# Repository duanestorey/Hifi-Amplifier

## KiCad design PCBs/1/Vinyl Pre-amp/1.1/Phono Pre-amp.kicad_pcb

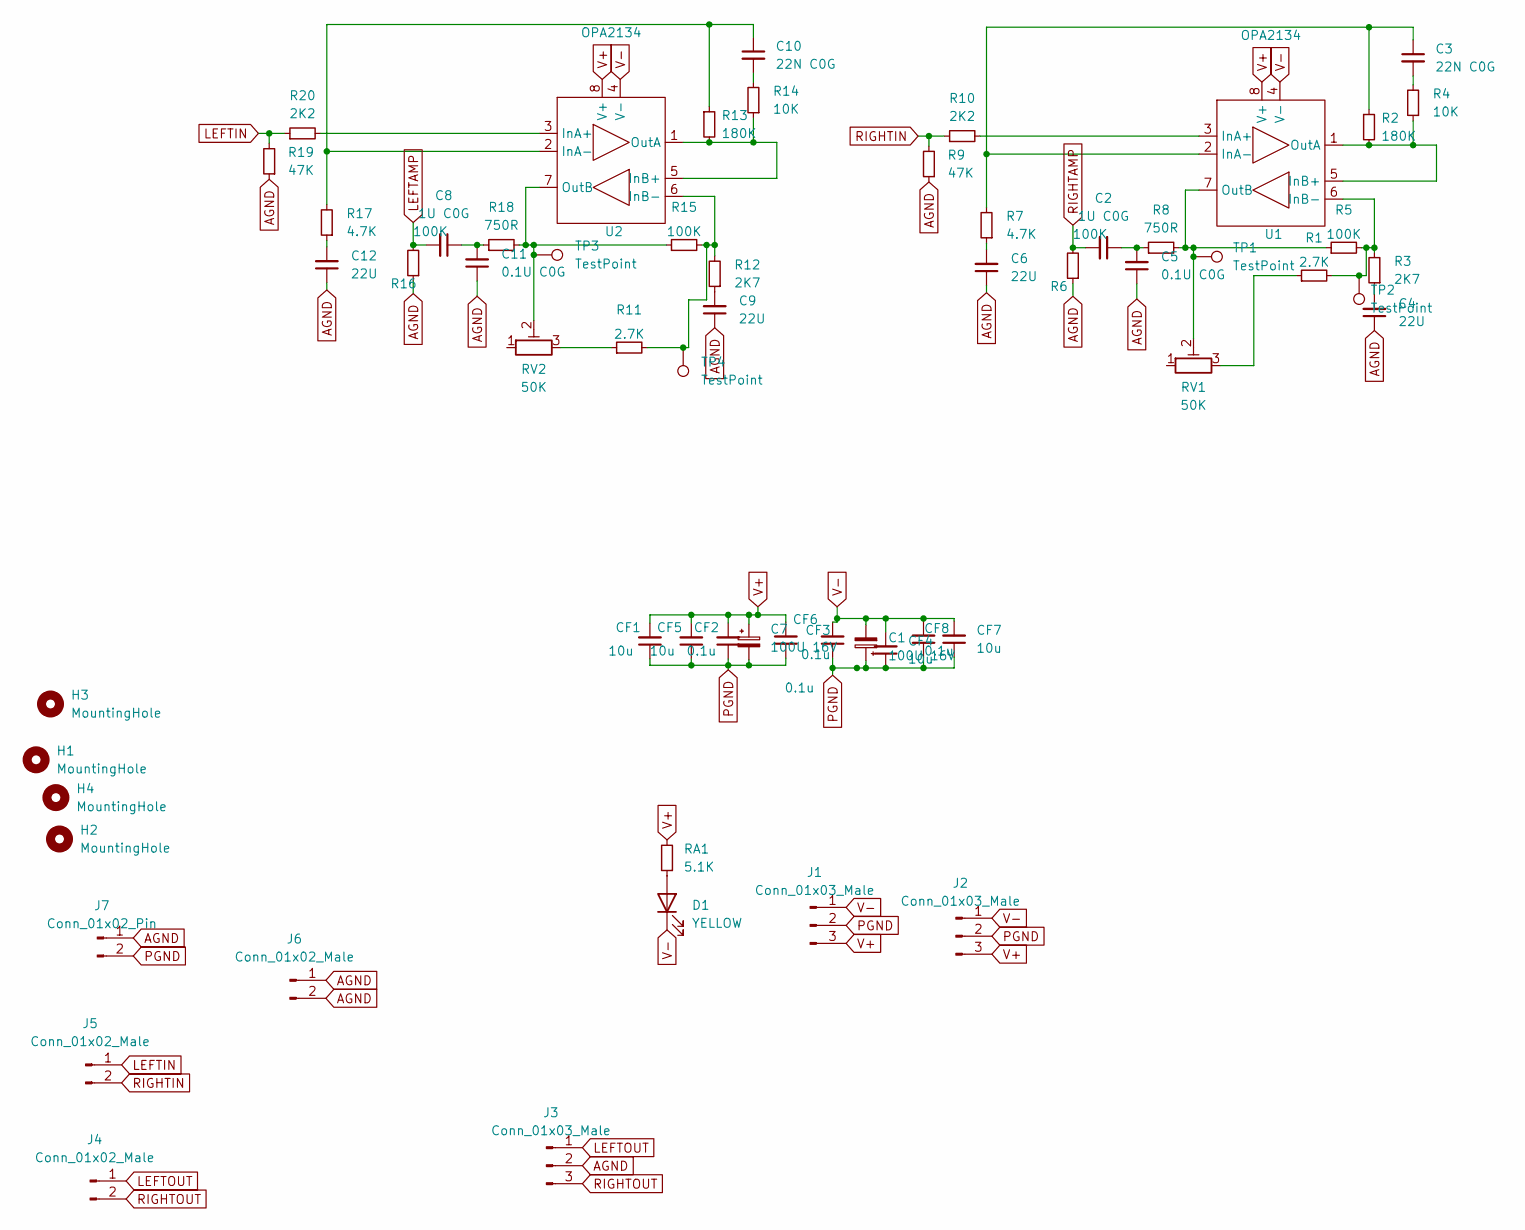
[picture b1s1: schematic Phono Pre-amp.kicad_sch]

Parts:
C1, C7: 100U 16V; CP_Radial_D6.3mm_P2.50mm
C2, C8: 1U C0G; CP_Radial_D5.0mm_P2.00mm
C3, C10: 22N C0G; C_0805_2012Metric_Pad1.18x1.45mm_HandSolder
C4, C6, C9, C12: 22U; CP_Radial_D6.3mm_P2.50mm
C5, C11: 0.1U C0G; C_1206_3216Metric_Pad1.33x1.80mm_HandSolder
CF1, CF4, CF5, CF7: 10u; C_1206_3216Metric_Pad1.33x1.80mm_HandSolder
CF2, CF3, CF6, CF8: 0.1u; C_0805_2012Metric_Pad1.18x1.45mm_HandSolder
D1: YELLOW; LED_0805_2012Metric_Pad1.15x1.40mm_HandSolder
H1, H2, H3, H4: MountingHole; MountingHole_3.2mm_M3
J1, J2: Conn_01x03_Male; JST_PH_B3B-PH-K_1x03_P2.00mm_Vertical
J3: Conn_01x03_Male; PinHeader_1x03_P2.54mm_Vertical
J4, J5, J6: Conn_01x02_Male; JST_PH_B2B-PH-K_1x02_P2.00mm_Vertical
J7: Conn_01x02_Pin; PinHeader_1x02_P2.54mm_Vertical
R1, R11: 2.7K; R_0805_2012Metric_Pad1.20x1.40mm_HandSolder
R2, R13: 180K; R_0805_2012Metric_Pad1.20x1.40mm_HandSolder
R3, R12: 2K7; R_0805_2012Metric_Pad1.20x1.40mm_HandSolder
R4, R14: 10K; R_0805_2012Metric_Pad1.20x1.40mm_HandSolder
R5, R6, R15, R16: 100K; R_0805_2012Metric_Pad1.20x1.40mm_HandSolder
R7, R17: 4.7K; R_0805_2012Metric_Pad1.20x1.40mm_HandSolder
R8, R18: 750R; R_0805_2012Metric_Pad1.20x1.40mm_HandSolder
R9, R19: 47K; R_0805_2012Metric_Pad1.20x1.40mm_HandSolder
R10, R20: 2K2; R_0805_2012Metric_Pad1.20x1.40mm_HandSolder
RA1: 5.1K; R_0603_1608Metric
RV1, RV2: 50K; Potentiometer_Bourns_3296W_Vertical
TP1, TP2, TP3, TP4: TestPoint; TestPoint_THTPad_1.5x1.5mm_Drill0.7mm
U1, U2: OPA2134; DIP-8_W7.62mm_Socket

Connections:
LEFTAMP: C8.2, J6.6, R16.2
LEFTOUT: J3.1, J4.1, J6.4
unnamed: C2.1, C5.2, R8.1
unnamed: C3.2, R4.2
unnamed: C4.2, R3.1
unnamed: C6.2, R7.1
unnamed: C9.2, R12.1
unnamed: C10.2, R14.2
unnamed: C8.1, C11.2, R18.1
unnamed: C12.2, R17.1
unnamed: D1.2 (A), RA1.1
unnamed: R1.1, RV1.3
unnamed: R11.1, RV2.3
unnamed: R10.2, U1.3 (InA+)
unnamed: C3.1, R2.1, R7.2, U1.2 (InA-)
unnamed: R2.2, R4.1, U1.1 (OutA), U1.5 (InB+)
unnamed: R1.2, R3.2, R5.2, TP2.1, U1.6 (InB-)
unnamed: R5.1, R8.2, RV1.2, TP1.1, U1.7 (OutB)
unnamed: R20.2, U2.3 (InA+)
unnamed: C10.1, R13.1, R17.2, U2.2 (InA-)
unnamed: R13.2, R14.1, U2.1 (OutA), U2.5 (InB+)
unnamed: R11.2, R12.2, R15.2, TP4.1, U2.6 (InB-)
unnamed: R15.1, R18.2, RV2.2, TP3.1, U2.7 (OutB)
RIGHTAMP: C2.2, J6.5, R6.2
RIGHTOUT: J3.3, J4.2, J6.3
V+: C7.1, CF1.2, CF2.2, CF5.2, CF6.2, J1.3, J2.3, RA1.2, U1.8 (V+), U2.8 (V+)
V-: C1.2, CF3.2, CF4.2, CF7.2, CF8.2, D1.1 (K), J1.1, J2.1, U1.4 (V-), U2.4 (V-)

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
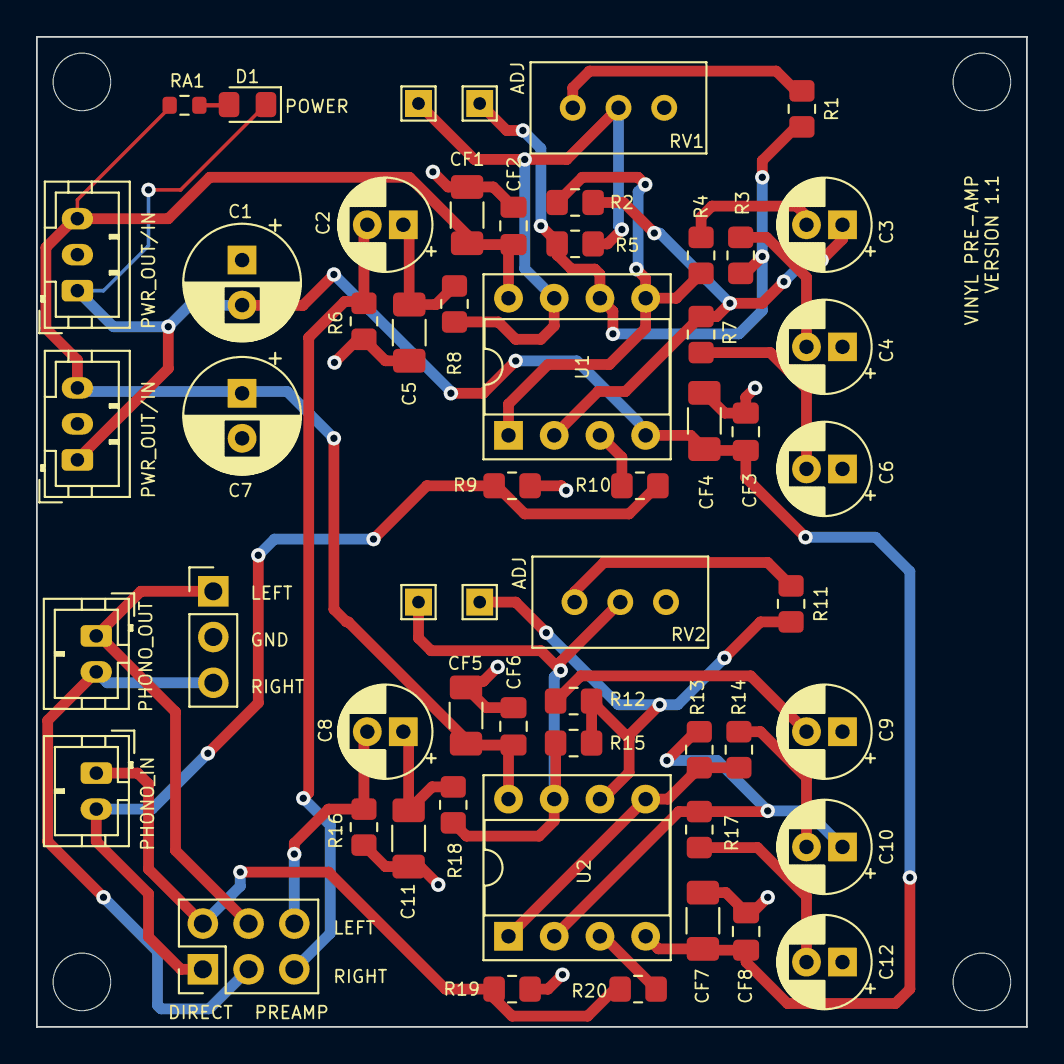
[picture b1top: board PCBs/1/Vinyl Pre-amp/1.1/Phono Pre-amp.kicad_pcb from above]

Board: 2 copper layers, 55.0 x 55.0 mm, 60 parts (0 on the bottom side), 30 nets.

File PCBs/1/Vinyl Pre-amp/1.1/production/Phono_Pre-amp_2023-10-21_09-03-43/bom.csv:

Designator,Footprint,Quantity,Value,LCSC Part #
"C1, C7",CP_Radial_D6.3mm_P2.50mm,2,100U 16V,
"C10, C3, C4, C9",CP_Radial_D5.0mm_P2.00mm,4,22U C0G,
"C11, C5",1206,2,0.1U C0G,
"C12, C6",CP_Radial_D5.0mm_P2.00mm,2,22U,
"C2, C8",CP_Radial_D5.0mm_P2.00mm,2,1U C0G,
"CF1, CF4, CF5, CF7",1206,4,10u,
"CF2, CF3, CF6, CF8",0805,4,0.1u,
D1,0805,1,YELLOW,
"H1, H2, H3, H4",MountingHole_3.2mm_M3,4,MountingHole,
"J1, J2",JST_PH_B3B-PH-K_1x03_P2.00mm_Vertical,2,Conn_01x03_Male,
J3,PinHeader_1x03_P2.54mm_Vertical,1,Conn_01x03_Male,
"J4, J5",JST_PH_B2B-PH-K_1x02_P2.00mm_Vertical,2,Conn_01x02_Male,
J6,PinHeader_2x03_P2.54mm_Vertical,1,Conn_02x03_Odd_Even,
"R1, R11",0805,2,2.7K,
"R10, R20",0805,2,2K2,
"R12, R3",0805,2,2K7,
"R13, R2",0805,2,180K,
"R14, R17, R4, R7",0805,4,4K7,
"R15, R16, R5, R6",0805,4,100K,
"R18, R8",0805,2,750R,
"R19, R9",0805,2,47K,
RA1,0603,1,5.1K,
"RV1, RV2",Potentiometer_Bourns_3296W_Vertical,2,50K,
"TP1, TP2, TP3, TP4",TestPoint_THTPad_1.5x1.5mm_Drill0.7mm,4,TestPoint,
"U1, U2",DIP-8_W7.62mm_Socket,2,OPA2134,

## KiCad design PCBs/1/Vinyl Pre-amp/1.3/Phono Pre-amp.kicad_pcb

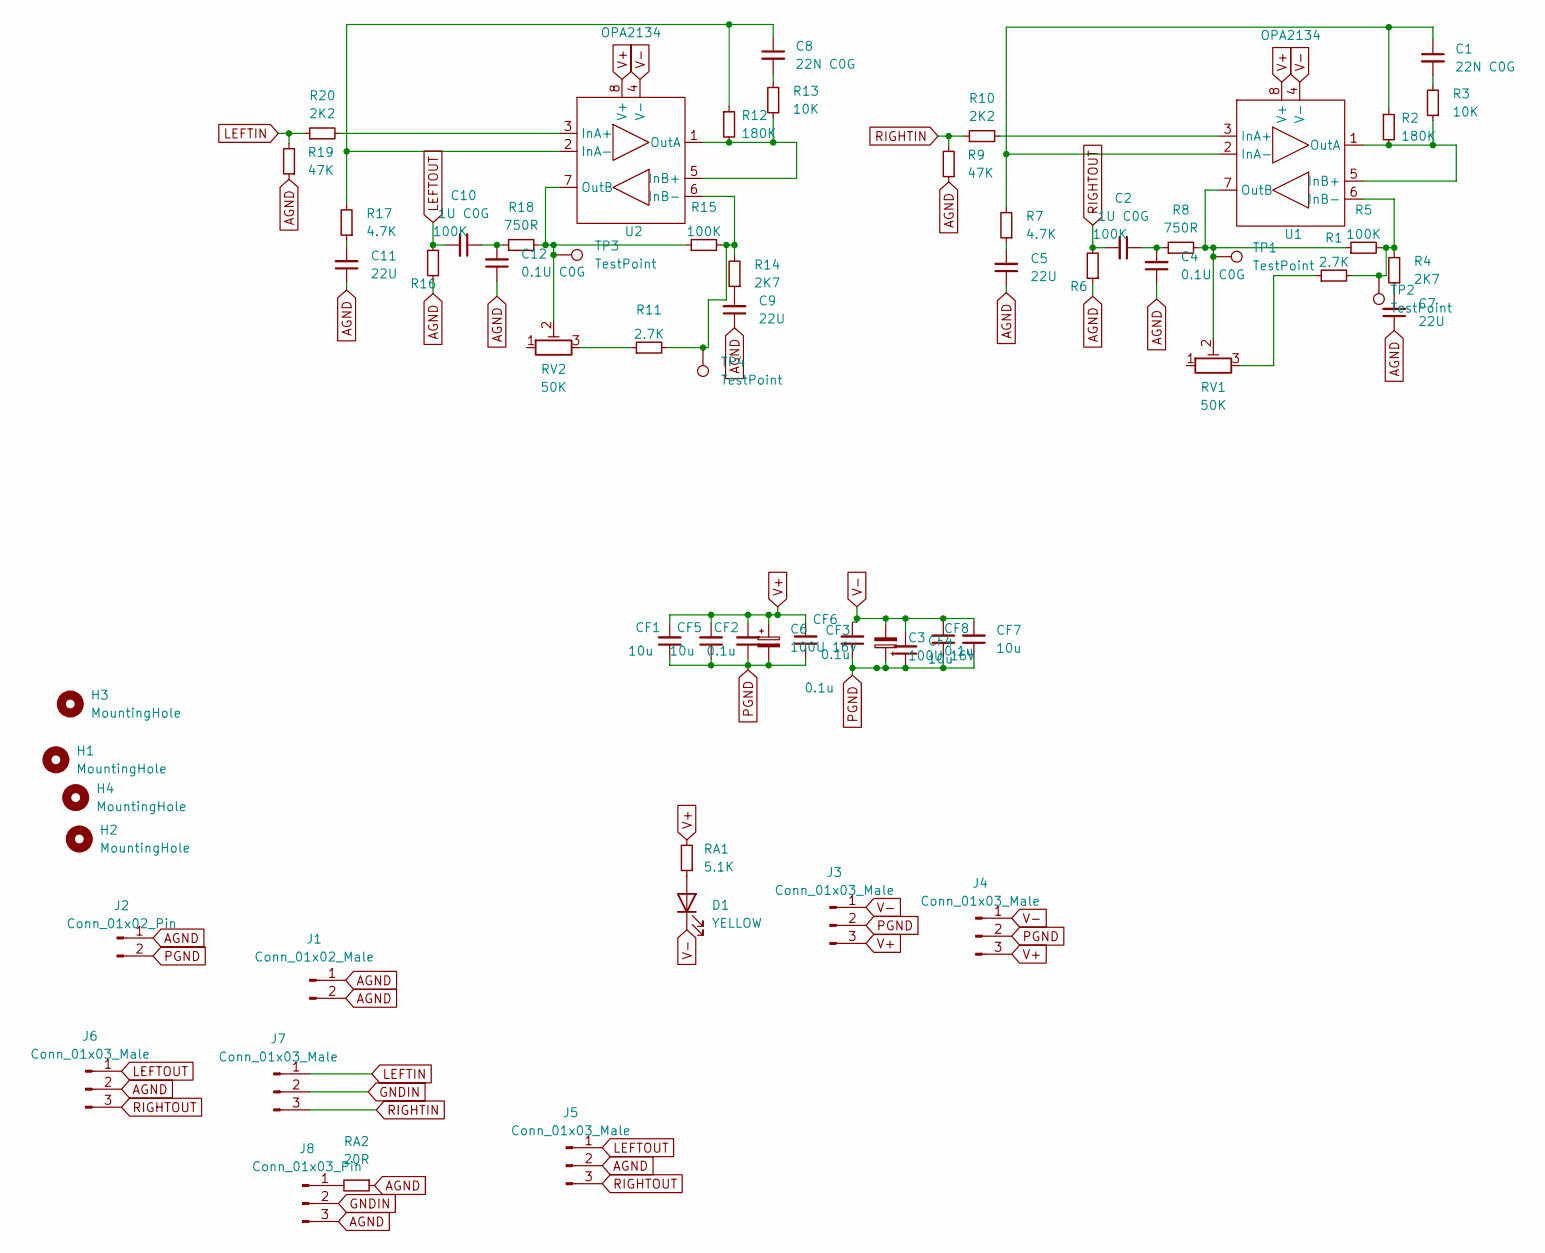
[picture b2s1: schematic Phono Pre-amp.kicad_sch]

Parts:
C1, C8: 22N C0G; C_0805_2012Metric_Pad1.18x1.45mm_HandSolder
C2, C10: 1U C0G; CP_Radial_D5.0mm_P2.00mm
C3, C6: 100U 16V; CP_Radial_D6.3mm_P2.50mm
C4, C12: 0.1U C0G; C_1206_3216Metric_Pad1.33x1.80mm_HandSolder
C5, C7, C9, C11: 22U; CP_Radial_D6.3mm_P2.50mm
CF1, CF4, CF5, CF7: 10u; C_1206_3216Metric_Pad1.33x1.80mm_HandSolder
CF2, CF3, CF6, CF8: 0.1u; C_0805_2012Metric_Pad1.18x1.45mm_HandSolder
D1: YELLOW; LED_0805_2012Metric_Pad1.15x1.40mm_HandSolder
H1, H2, H3, H4: MountingHole; MountingHole_3.2mm_M3
J1: Conn_01x02_Male; JST_PH_B2B-PH-K_1x02_P2.00mm_Vertical
J2: Conn_01x02_Pin; PinHeader_1x02_P2.54mm_Vertical
J3, J4, J6, J7: Conn_01x03_Male; JST_PH_B3B-PH-K_1x03_P2.00mm_Vertical
J5: Conn_01x03_Male; PinHeader_1x03_P2.54mm_Vertical
J8: Conn_01x03_Pin; PinHeader_1x03_P2.54mm_Vertical
R1, R11: 2.7K; R_0805_2012Metric_Pad1.20x1.40mm_HandSolder
R2, R12: 180K; R_0805_2012Metric_Pad1.20x1.40mm_HandSolder
R3, R13: 10K; R_0805_2012Metric_Pad1.20x1.40mm_HandSolder
R4, R14: 2K7; R_0805_2012Metric_Pad1.20x1.40mm_HandSolder
R5, R6, R15, R16: 100K; R_0805_2012Metric_Pad1.20x1.40mm_HandSolder
R7, R17: 4.7K; R_0805_2012Metric_Pad1.20x1.40mm_HandSolder
R8, R18: 750R; R_0805_2012Metric_Pad1.20x1.40mm_HandSolder
R9, R19: 47K; R_0805_2012Metric_Pad1.20x1.40mm_HandSolder
R10, R20: 2K2; R_0805_2012Metric_Pad1.20x1.40mm_HandSolder
RA1: 5.1K; R_0603_1608Metric
RA2: 20R; R_0603_1608Metric
RV1, RV2: 50K; Potentiometer_Bourns_3296W_Vertical
TP1, TP2, TP3, TP4: TestPoint; TestPoint_THTPad_1.5x1.5mm_Drill0.7mm
U1, U2: OPA2134; DIP-8_W7.62mm_Socket

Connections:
AGND: C4.1, C5.1, C7.1, C9.1, C11.1, C12.1, J1.1, J1.2, J2.1, J5.2, J6.2, J8.3, R6.1, R9.1, R16.1, R19.1, RA2.1
GNDIN: J7.2, J8.2
LEFTIN: J7.1, R19.2, R20.1
LEFTOUT: C10.2, J5.1, J6.1, R16.2
unnamed: C1.2, R3.2
unnamed: C2.1, C4.2, R8.1
unnamed: C5.2, R7.1
unnamed: C7.2, R4.1
unnamed: C8.2, R13.2
unnamed: C9.2, R14.1
unnamed: C10.1, C12.2, R18.1
unnamed: C11.2, R17.1
unnamed: D1.2 (A), RA1.1
unnamed: J8.1, RA2.2
unnamed: R1.1, RV1.3
unnamed: R11.1, RV2.3
unnamed: R10.2, U1.3 (InA+)
unnamed: C1.1, R2.1, R7.2, U1.2 (InA-)
unnamed: R2.2, R3.1, U1.1 (OutA), U1.5 (InB+)
unnamed: R1.2, R4.2, R5.2, TP2.1, U1.6 (InB-)
unnamed: R5.1, R8.2, RV1.2, TP1.1, U1.7 (OutB)
unnamed: R20.2, U2.3 (InA+)
unnamed: C8.1, R12.1, R17.2, U2.2 (InA-)
unnamed: R12.2, R13.1, U2.1 (OutA), U2.5 (InB+)
unnamed: R11.2, R14.2, R15.2, TP4.1, U2.6 (InB-)
unnamed: R15.1, R18.2, RV2.2, TP3.1, U2.7 (OutB)
PGND: C3.1, C6.2, CF1.1, CF2.1, CF3.1, CF4.1, CF5.1, CF6.1, CF7.1, CF8.1, J2.2, J3.2, J4.2
RIGHTIN: J7.3, R9.2, R10.1
RIGHTOUT: C2.2, J5.3, J6.3, R6.2
V+: C6.1, CF1.2, CF2.2, CF5.2, CF6.2, J3.3, J4.3, RA1.2, U1.8 (V+), U2.8 (V+)
V-: C3.2, CF3.2, CF4.2, CF7.2, CF8.2, D1.1 (K), J3.1, J4.1, U1.4 (V-), U2.4 (V-)

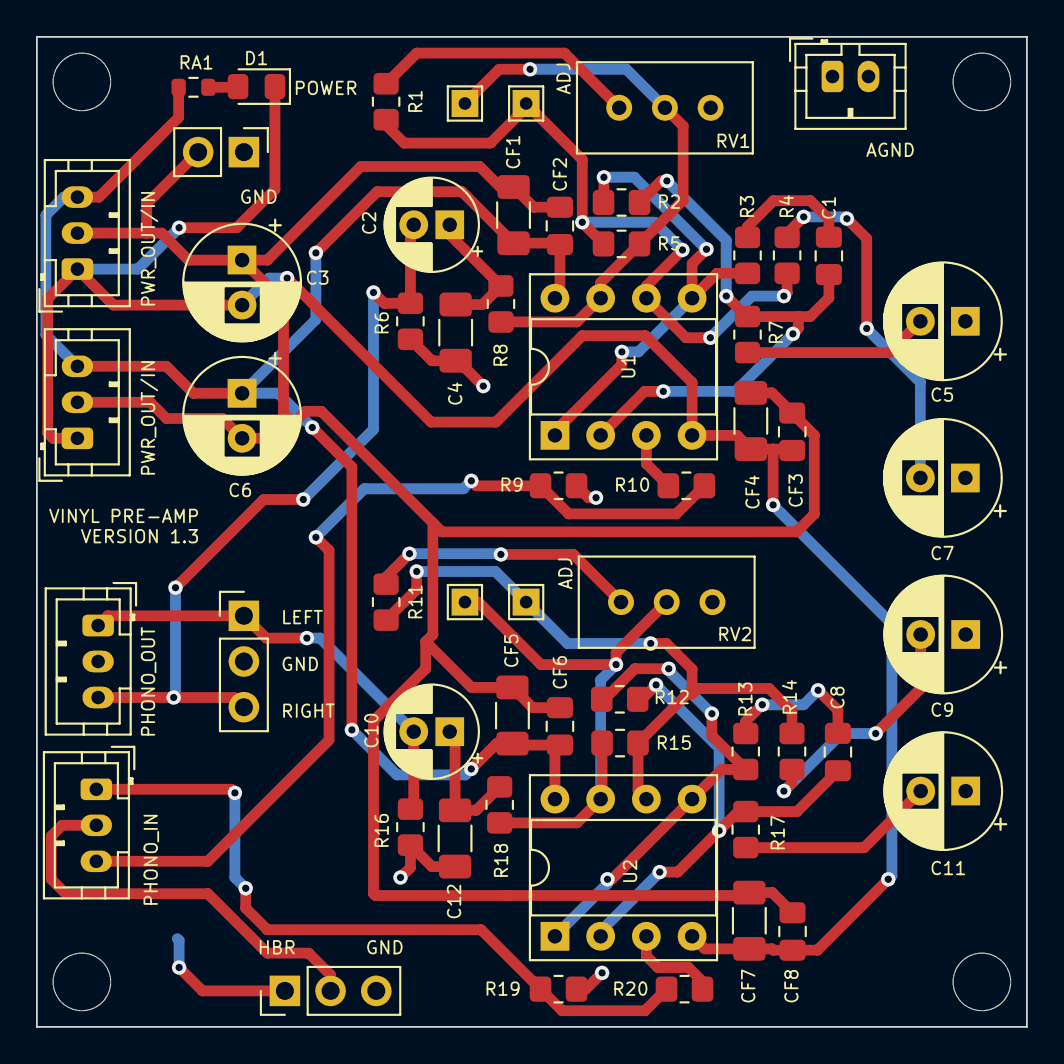
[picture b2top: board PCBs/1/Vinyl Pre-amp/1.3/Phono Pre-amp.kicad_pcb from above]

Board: 2 copper layers, 55.0 x 55.0 mm, 63 parts (1 on the bottom side), 31 nets.

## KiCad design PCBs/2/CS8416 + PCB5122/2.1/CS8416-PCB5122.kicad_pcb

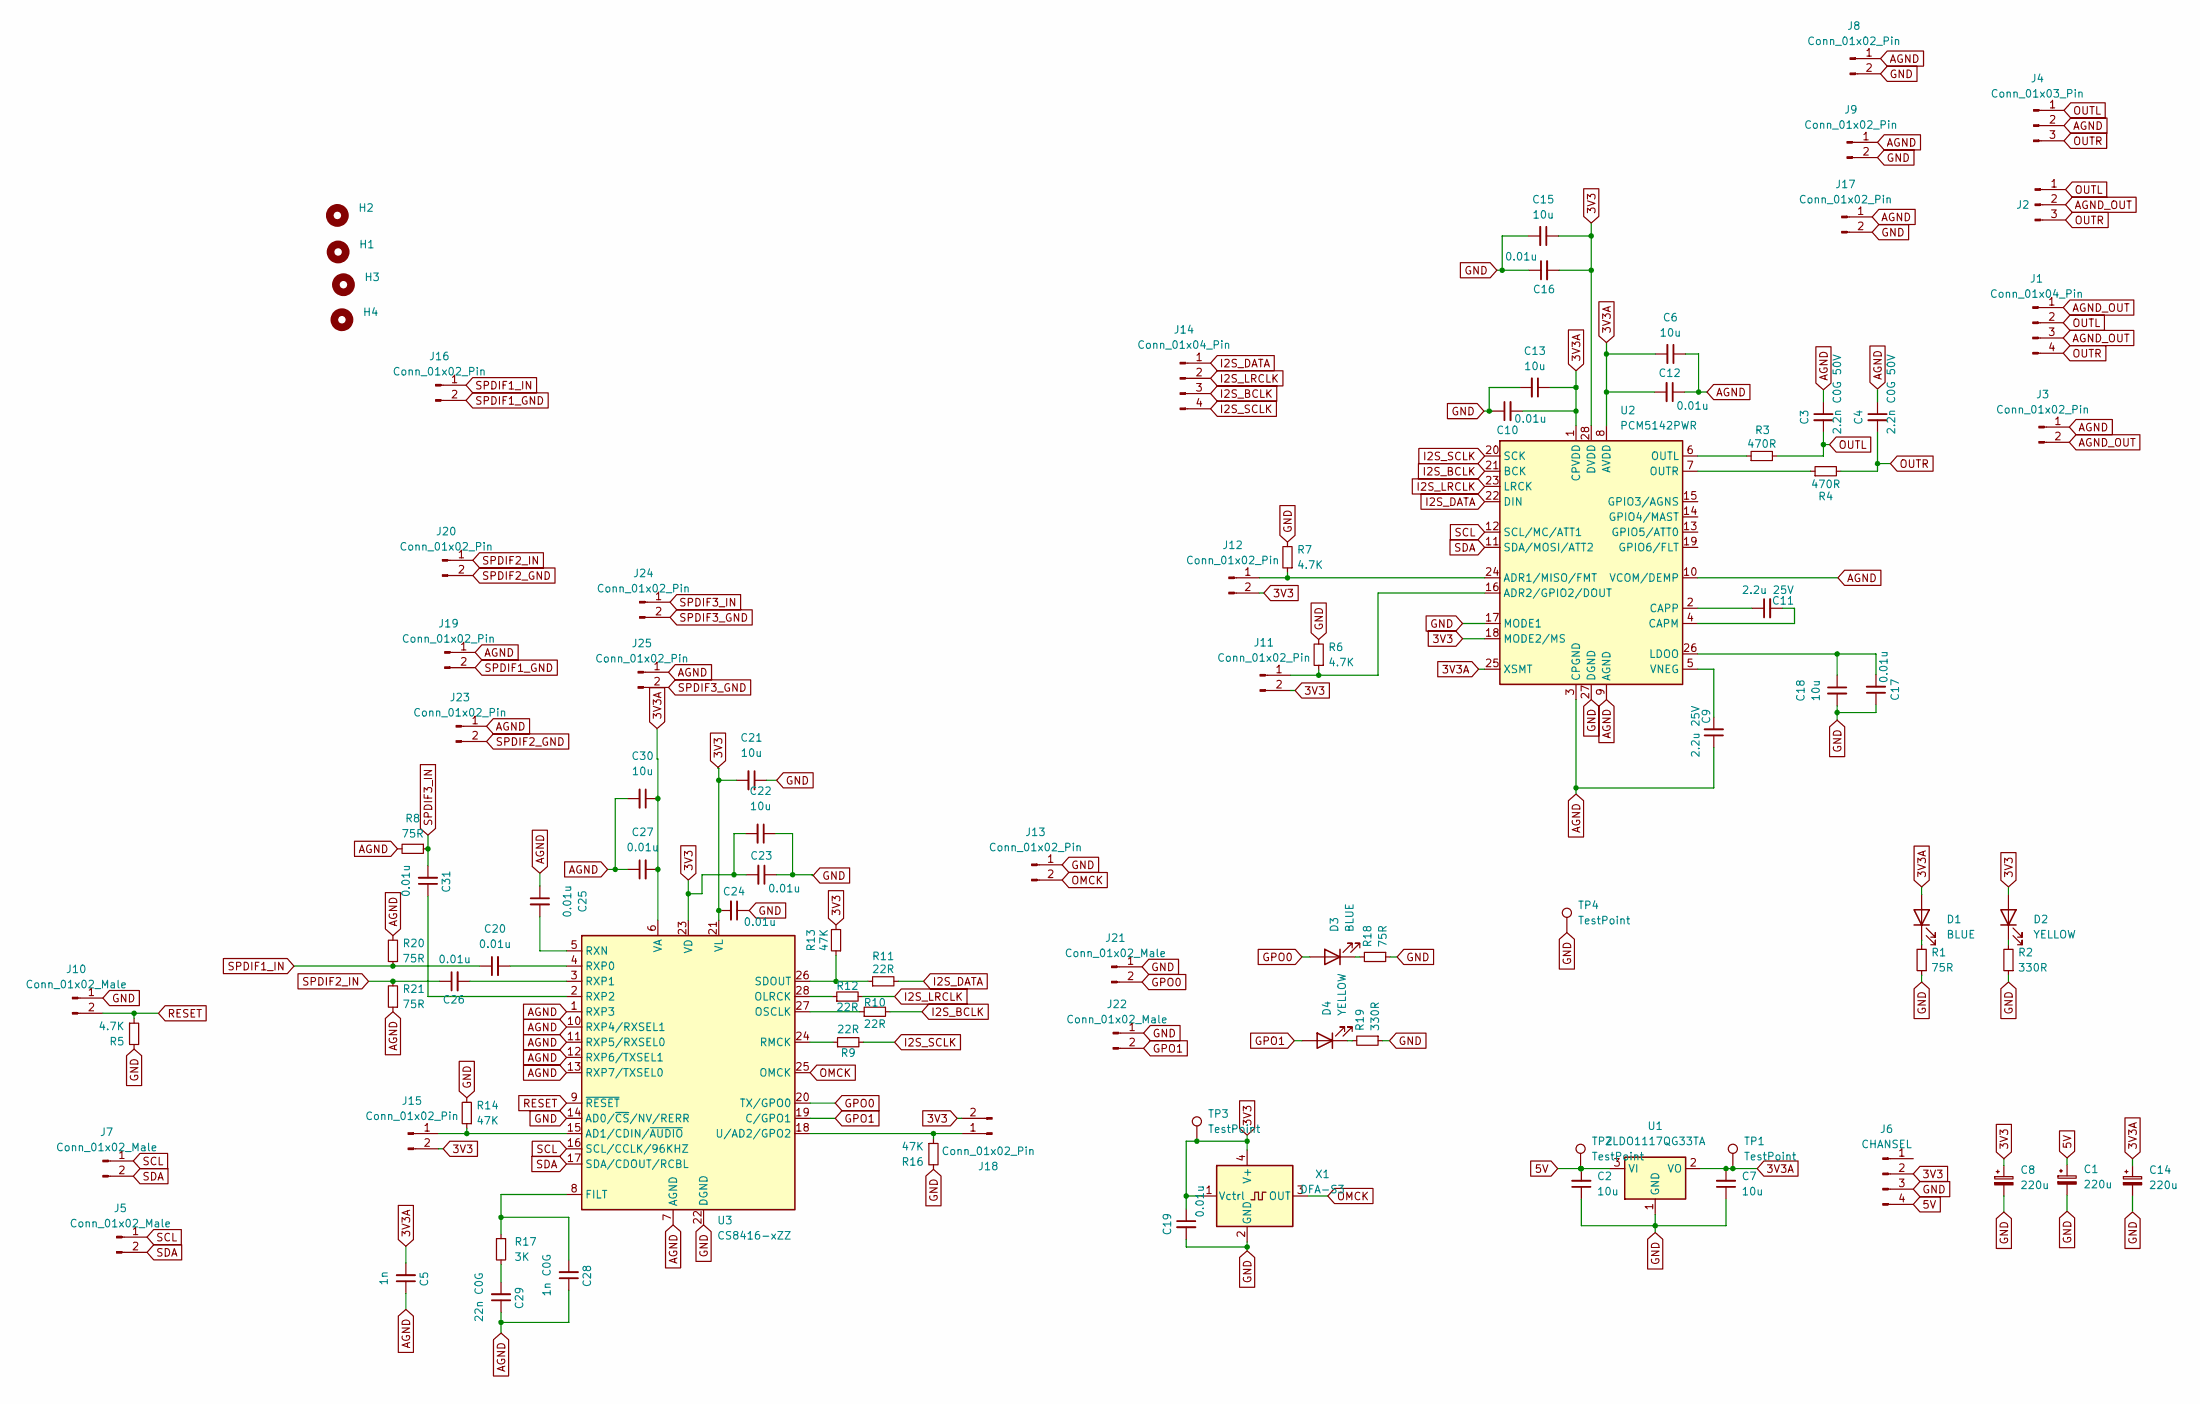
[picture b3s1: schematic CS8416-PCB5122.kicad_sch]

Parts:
C1, C8, C14: 220u; CP_Radial_D6.3mm_P2.50mm
C2, C6, C7, C13, C15, C18, C21, C22, C30: 10u; C_1206_3216Metric_Pad1.33x1.80mm_HandSolder
C3, C4: 2.2n C0G 50V; C_0805_2012Metric
C5: 1n; C_0805_2012Metric_Pad1.18x1.45mm_HandSolder
C9, C11: 2.2u 25V; C_0805_2012Metric
C10, C12, C16, C17, C19, C23, C24, C27: 0.01u; C_0805_2012Metric
C20, C25, C26, C31: 0.01u; C_0805_2012Metric_Pad1.18x1.45mm_HandSolder
C28: 1n C0G; C_0805_2012Metric_Pad1.18x1.45mm_HandSolder
C29: 22n C0G; C_0805_2012Metric_Pad1.18x1.45mm_HandSolder
D1, D3: BLUE; LED_0805_2012Metric_Pad1.15x1.40mm_HandSolder
D2, D4: YELLOW; LED_0805_2012Metric_Pad1.15x1.40mm_HandSolder
H1, H2, H3, H4: MountingHole; MountingHole_3.2mm_M3
J1: Conn_01x04_Pin; JST_PH_B4B-PH-K_1x04_P2.00mm_Vertical
J2: Conn_01x03_Pin; JST_PH_B3B-PH-K_1x03_P2.00mm_Vertical
J3, J8, J9, J11, J12, J13, J15, J17, J18, J19, J23, J25: Conn_01x02_Pin; PinHeader_1x02_P2.54mm_Vertical
J4: Conn_01x03_Pin; PinHeader_1x03_P2.54mm_Vertical
J5, J7, J10, J21, J22: Conn_01x02_Male; JST_PH_B2B-PH-K_1x02_P2.00mm_Vertical
J6: CHANSEL; JST_XH_B4B-XH-A_1x04_P2.50mm_Vertical
J14: Conn_01x04_Pin; PinHeader_1x04_P2.54mm_Vertical
J16, J20, J24: Conn_01x02_Pin; JST_XH_B2B-XH-A_1x02_P2.50mm_Vertical
R1, R8, R18, R20, R21: 75R; R_0603_1608Metric_Pad0.98x0.95mm_HandSolder
R2, R19: 330R; R_0603_1608Metric_Pad0.98x0.95mm_HandSolder
R3, R4: 470R; R_0603_1608Metric_Pad0.98x0.95mm_HandSolder
R5, R6, R7: 4.7K; R_0603_1608Metric_Pad0.98x0.95mm_HandSolder
R9, R10, R11, R12: 22R; R_0603_1608Metric_Pad0.98x0.95mm_HandSolder
R13, R14, R16: 47K; R_0603_1608Metric_Pad0.98x0.95mm_HandSolder
R17: 3K; R_0805_2012Metric_Pad1.20x1.40mm_HandSolder
TP1, TP2, TP3, TP4: TestPoint; TestPoint_Pad_2.0x2.0mm
U1: ZLDO1117QG33TA; SOT-223-3_TabPin2
U2: PCM5142PWR; TSSOP-28_4.4x9.7mm_P0.65mm
U3: CS8416-xZZ; TSSOP-28_4.4x9.7mm_P0.65mm
X1: DFA-S3; Oscillator_SMD_EuroQuartz_XO53-4Pin_5.0x3.2mm

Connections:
3V3: C8.1, C15.1, C16.2, C19.1, C21.2, C22.2, C23.2, C24.2, D2.2 (A), J6.2, J11.2, J12.2, J15.2, J18.2, R13.2, TP3.1, U2.18 (MODE2/MS), U2.28 (DVDD), U3.21 (VL), U3.23 (VD), X1.1 (Vctrl), X1.4 (V+)
3V3A: C5.2, C6.2, C7.2, C10.2, C12.2, C13.1, C14.1, C27.2, C30.1, D1.2 (A), TP1.1, U1.2 (VO), U2.1 (CPVDD), U2.8 (AVDD), U2.25 (XSMT), U3.6 (VA)
5V: C1.1, C2.2, J6.4, TP2.1, U1.3 (VI)
AGND: C3.1, C4.1, C5.1, C6.1, C9.1, C12.1, C25.1, C27.1, C28.1, C29.1, C30.2, J3.1, J4.2, J8.1, J9.1, J17.1, J19.1, J23.1, J25.1, R8.2, R20.2, R21.1, U2.3 (CPGND), U2.9 (AGND), U2.10 (VCOM/DEMP), U3.1 (RXP3), U3.7 (AGND), U3.10 (RXP4/RXSEL1), U3.11 (RXP5/RXSEL0), U3.12 (RXP6/TXSEL1), U3.13 (RXP7/TXSEL0)
AGND_OUT: J1.1, J1.3, J2.2, J3.2
GND: C1.2, C2.1, C7.1, C8.2, C10.1, C13.2, C14.2, C15.2, C16.1, C17.1, C18.2, C19.2, C21.1, C22.1, C23.1, C24.1, J6.3, J8.2, J9.2, J10.1, J13.1, J17.2, J21.1, J22.1, R1.1, R2.1, R5.2, R6.2, R7.2, R14.2, R16.2, R18.1, R19.1, TP4.1, U1.1 (GND), U2.17 (MODE1), U2.27 (DGND), U3.14 (AD0/~CS/NV/RERR), U3.22 (DGND), X1.2 (GND)
GPO0: D3.2 (A), J21.2, U3.20 (TX/GPO0)
GPO1: D4.2 (A), J22.2, U3.19 (C/GPO1)
I2S_BCLK: J14.3, R10.2, U2.21 (BCK)
I2S_DATA: J14.1, R11.2, U2.22 (DIN)
I2S_LRCLK: J14.2, R12.2, U2.23 (LRCK)
I2S_SCLK: J14.4, R9.2, U2.20 (SCK)
unnamed: C29.2, R17.2
unnamed: D1.1 (K), R1.2
unnamed: D2.1 (K), R2.2
unnamed: D3.1 (K), R18.2
unnamed: D4.1 (K), R19.2
unnamed: J11.1, R6.1, U2.16 (ADR2/GPIO2/DOUT)
unnamed: J12.1, R7.1, U2.24 (ADR1/MISO/FMT)
unnamed: J15.1, R14.1, U3.15 (AD1/CDIN/~AUDIO)
unnamed: J18.1, R16.1, U3.18 (U/AD2/GPO2)
unnamed: C11.2, U2.4 (CAPM)
unnamed: C11.1, U2.2 (CAPP)
unnamed: C17.2, C18.1, U2.26 (LDOO)
unnamed: R3.1, U2.6 (OUTL)
unnamed: R4.1, U2.7 (OUTR)
unnamed: C9.2, U2.5 (VNEG)
unnamed: C28.2, R17.1, U3.8 (FILT)
unnamed: R12.1, U3.28 (OLRCK)
unnamed: R10.1, U3.27 (OSCLK)
unnamed: R9.1, U3.24 (RMCK)
unnamed: C25.2, U3.5 (RXN)
unnamed: C20.2, U3.4 (RXP0)
unnamed: C26.2, U3.3 (RXP1)
unnamed: C31.1, U3.2 (RXP2)
unnamed: R11.1, R13.1, U3.26 (SDOUT)
OMCK: J13.2, U3.25 (OMCK), X1.3 (OUT)
OUTL: C3.2, J1.2, J2.1, J4.1, R3.2
OUTR: C4.2, J1.4, J2.3, J4.3, R4.2
RESET: J10.2, R5.1, U3.9 (~RESET)
SCL: J5.1, J7.1, U2.12 (SCL/MC/ATT1), U3.16 (SCL/CCLK/96KHZ)
SDA: J5.2, J7.2, U2.11 (SDA/MOSI/ATT2), U3.17 (SDA/CDOUT/RCBL)
SPDIF1_GND: J16.2, J19.2
SPDIF1_IN: C20.1, J16.1, R20.1
SPDIF2_GND: J20.2, J23.2
SPDIF2_IN: C26.1, J20.1, R21.2
SPDIF3_GND: J24.2, J25.2
SPDIF3_IN: C31.2, J24.1, R8.1

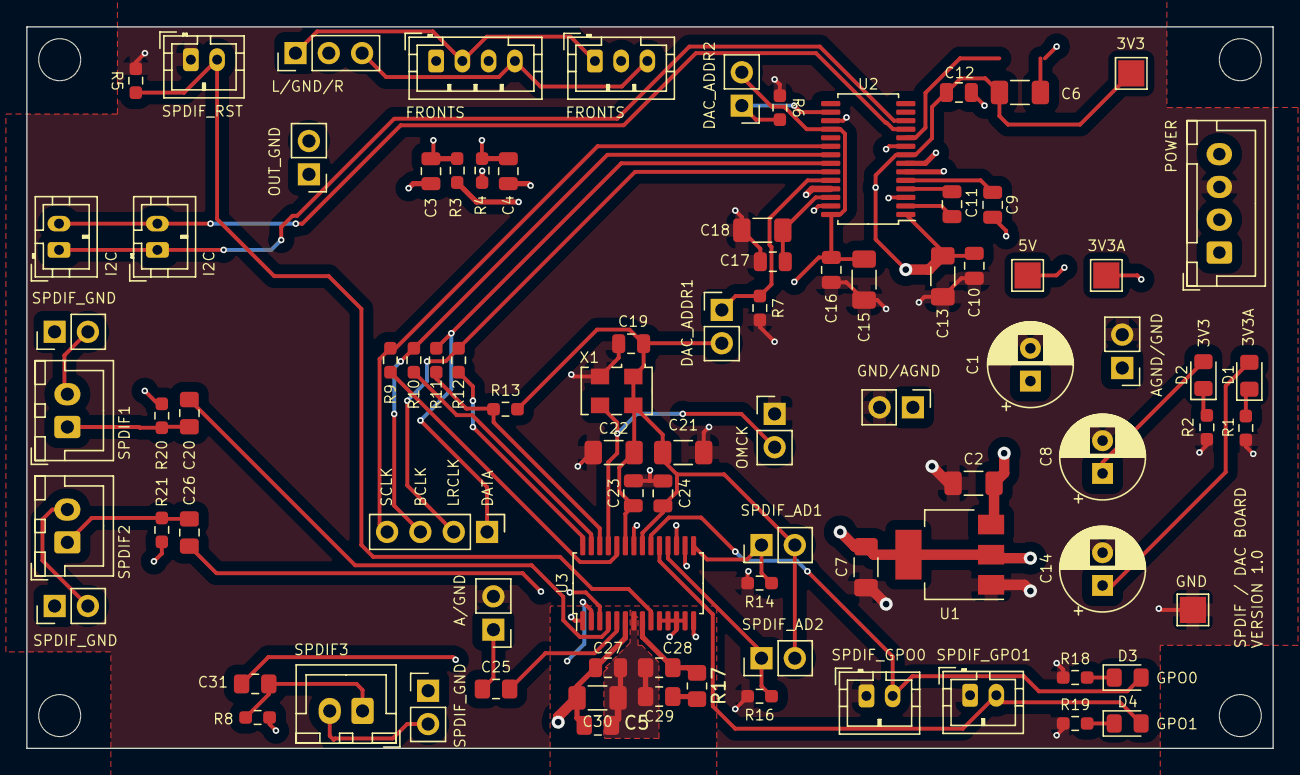
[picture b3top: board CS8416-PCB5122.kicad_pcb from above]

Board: 4 copper layers, 95.0 x 55.0 mm, 92 parts (0 on the bottom side), 48 nets.

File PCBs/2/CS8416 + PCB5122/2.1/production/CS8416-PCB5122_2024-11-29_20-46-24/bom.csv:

Designator,Footprint,Quantity,Value,LCSC Part #
"C1, C14, C8",CP_Radial_D6.3mm_P2.50mm,3,220u,
"C10, C12, C16, C17, C19, C20, C23, C24, C25, C26, C27, C31",0805,12,0.01u,
"C11, C9",0805,2,2.2u 25V,
"C13, C15, C18, C2, C21, C22, C30, C6, C7",1206,9,10u,
C28,0805,1,1n C0G,
C29,0805,1,22n C0G,
"C3, C4",0805,2,2.2n C0G 50V,
C5,1206,1,0R,
"D1, D3",0805,2,BLUE,
"D2, D4",0805,2,YELLOW,
"H1, H2, H3, H4",MountingHole_3.2mm_M3,4,MountingHole,
J1,JST_PH_B4B-PH-K_1x04_P2.00mm_Vertical,1,Conn_01x04_Pin,
"J10, J21, J22, J5, J7",JST_PH_B2B-PH-K_1x02_P2.00mm_Vertical,5,Conn_01x02_Male,
"J11, J12, J13, J15, J17, J18, J19, J23, J25, J3, J8, J9",PinHeader_1x02_P2.54mm_Vertical,12,Conn_01x02_Pin,
J14,PinHeader_1x04_P2.54mm_Vertical,1,Conn_01x04_Pin,
"J16, J20, J24",JST_XH_B2B-XH-A_1x02_P2.50mm_Vertical,3,Conn_01x02_Pin,
J2,JST_PH_B3B-PH-K_1x03_P2.00mm_Vertical,1,Conn_01x03_Pin,
J4,PinHeader_1x03_P2.54mm_Vertical,1,Conn_01x03_Pin,
J6,JST_XH_B4B-XH-A_1x04_P2.50mm_Vertical,1,CHANSEL,
"R1, R18, R20, R21, R8",0603,5,75R,
"R10, R11, R12, R9",0603,4,22R,
"R13, R14, R16",0603,3,47K,
R17,0603,1,3K,
"R19, R2",0603,2,330R,
"R3, R4",0603,2,470R,
"R5, R6, R7",0603,3,4.7K,
"TP1, TP2, TP3, TP4",TestPoint_Pad_2.0x2.0mm,4,TestPoint,
U1,SOT-223-3_TabPin2,1,ZLDO1117QG33TA,
U2,TSSOP-28_4.4x9.7mm_P0.65mm,1,PCM5142PWR,
U3,TSSOP-28_4.4x9.7mm_P0.65mm,1,CS8416-xZZ,
X1,Oscillator_SMD_EuroQuartz_XO53-4Pin_5.0x3.2mm,1,DFA-S3,

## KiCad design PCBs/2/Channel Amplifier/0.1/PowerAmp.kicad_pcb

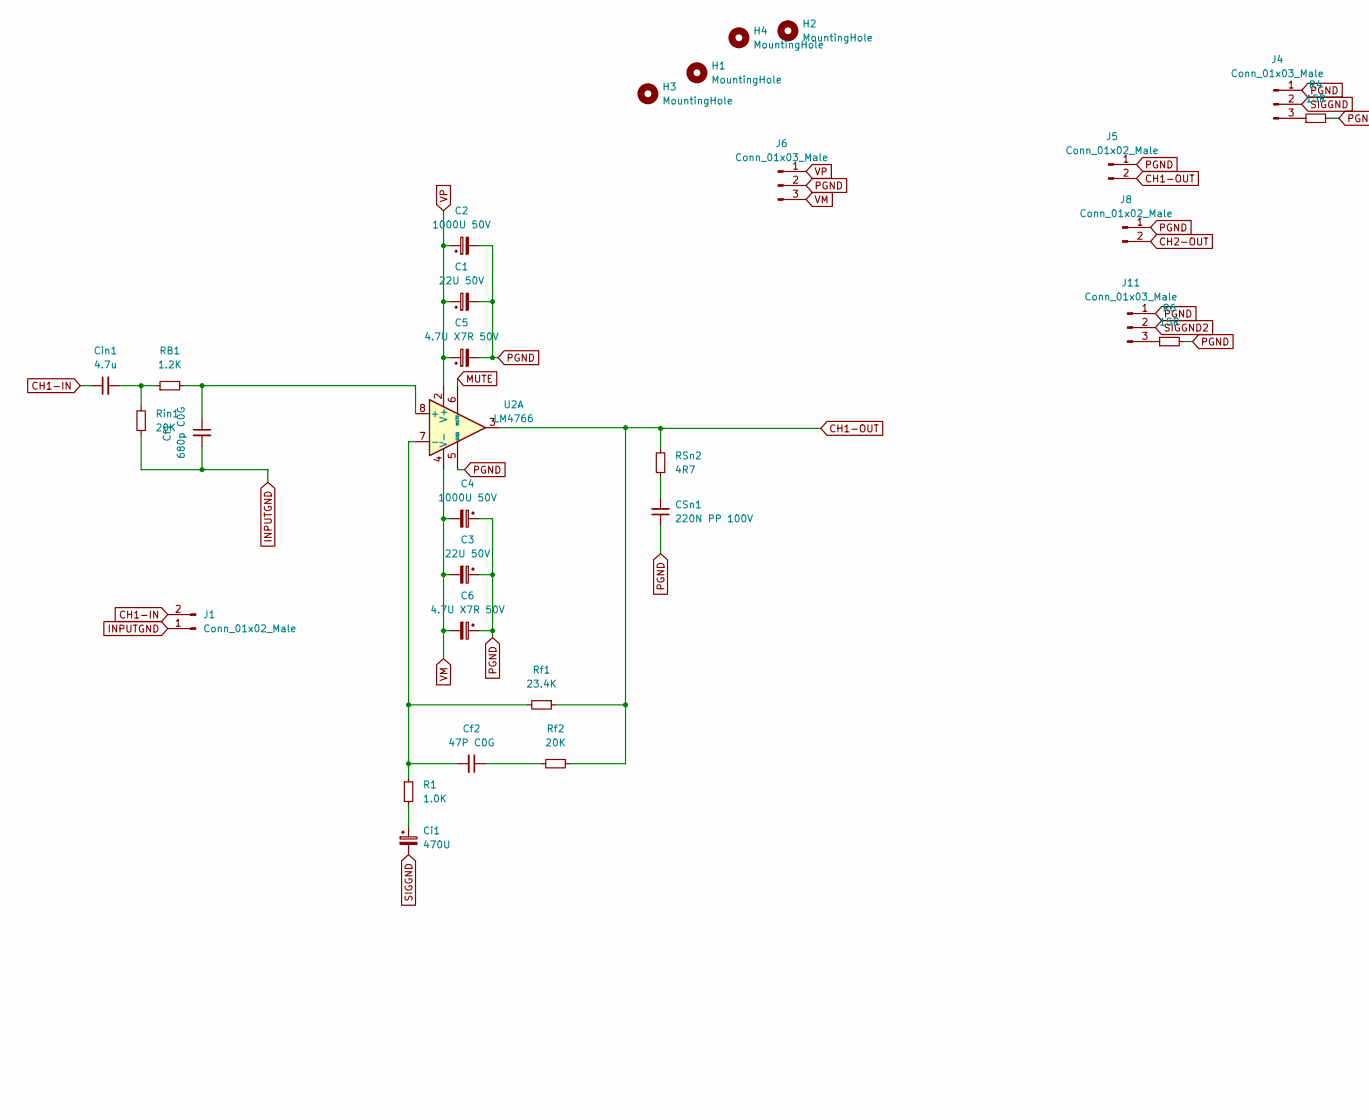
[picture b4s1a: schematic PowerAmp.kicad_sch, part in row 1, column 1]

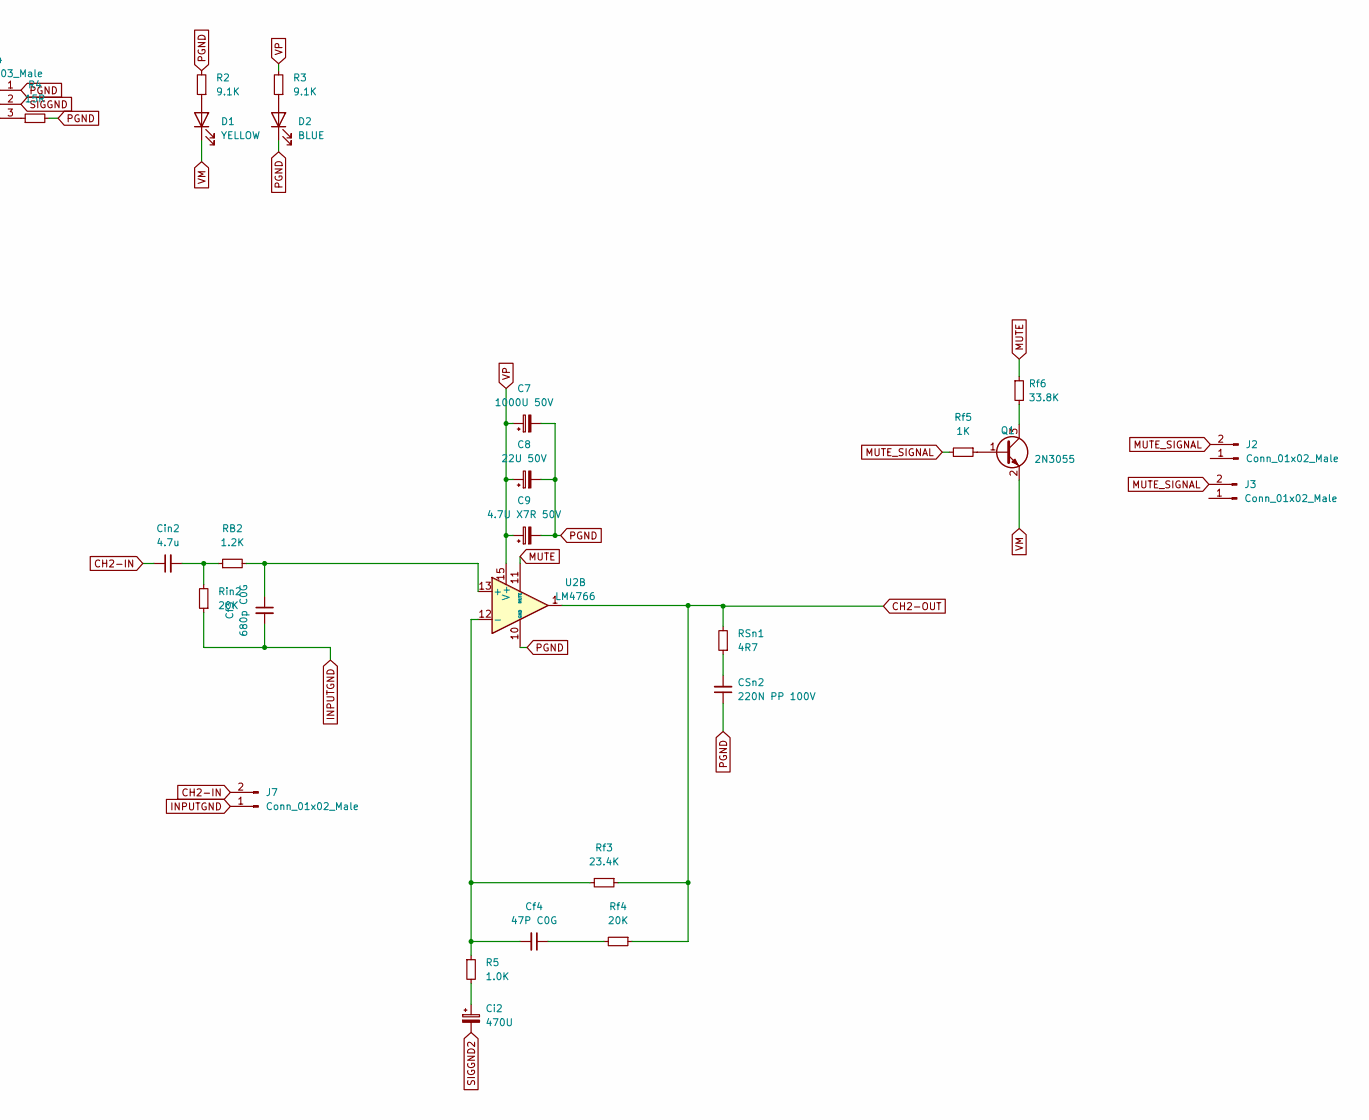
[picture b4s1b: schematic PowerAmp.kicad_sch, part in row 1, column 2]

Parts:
C1, C3, C8: 22U 50V; CP_Radial_D6.3mm_P2.50mm
C2, C4, C7: 1000U 50V; CP_Radial_D12.5mm_P5.00mm
C5, C6, C9: 4.7U X7R 50V; C_1206_3216Metric_Pad1.33x1.80mm_HandSolder
CSn1, CSn2: 220N PP 100V; C_Rect_L18.0mm_W7.0mm_P15.00mm_FKS3_FKP3
Cf1, Cf3: 680p C0G; C_1206_3216Metric_Pad1.33x1.80mm_HandSolder
Cf2, Cf4: 47P C0G; C_1206_3216Metric_Pad1.33x1.80mm_HandSolder
Ci1, Ci2: 470U; CP_Radial_D12.5mm_P5.00mm
Cin1, Cin2: 4.7u; 4.7uF Polypropylene Aliexpress
D1: YELLOW; LED_0805_2012Metric_Pad1.15x1.40mm_HandSolder
D2: BLUE; LED_0805_2012Metric_Pad1.15x1.40mm_HandSolder
H1, H2, H3, H4: MountingHole; MountingHole_3mm
J1, J2, J3, J7: Conn_01x02_Male; JST_PH_B2B-PH-K_1x02_P2.00mm_Vertical
J4, J11: Conn_01x03_Male; PinHeader_1x03_P2.54mm_Vertical
J5, J8: Conn_01x02_Male; JST_VH_B2P-VH_1x02_P3.96mm_Vertical
J6: Conn_01x03_Male; JST_VH_B3P-VH-B_1x03_P3.96mm_Vertical
Q1: 2N3055; TSOT-23
R1, R5: 1.0K; R_1206_3216Metric_Pad1.30x1.75mm_HandSolder
R2, R3: 9.1K; R_0805_2012Metric_Pad1.20x1.40mm_HandSolder
R4, R6: 15R; R_0805_2012Metric_Pad1.20x1.40mm_HandSolder
RB1, RB2: 1.2K; R_1206_3216Metric_Pad1.30x1.75mm_HandSolder
RSn1, RSn2: 4R7; R_Axial_DIN0411_L9.9mm_D3.6mm_P12.70mm_Horizontal
Rf1, Rf3: 23.4K; R_1206_3216Metric_Pad1.30x1.75mm_HandSolder
Rf2, Rf4: 20K; R_1206_3216Metric_Pad1.30x1.75mm_HandSolder
Rf5: 1K; R_0603_1608Metric_Pad0.98x0.95mm_HandSolder
Rf6: 33.8K; R_0603_1608Metric_Pad0.98x0.95mm_HandSolder
Rin1, Rin2: 20K; R_1206_3216Metric_Pad1.30x1.75mm_HandSolder
U2: LM4766; TO-220-15_P2.54x2.54mm_StaggerOdd_Lead4.58mm_Vertical

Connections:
CH1-IN: Cin1.1, J1.2
CH1-OUT: J5.2, RSn2.2, Rf1.1, Rf2.1, U2.3
CH2-IN: Cin2.1, J7.2
CH2-OUT: J8.2, RSn1.2, Rf3.1, Rf4.1, U2.1
INPUTGND: Cf1.2, Cf3.2, J1.1, J7.1, Rin1.1, Rin2.1
MUTE: Rf6.1, U2.6 (MUTE), U2.11 (MUTE)
MUTE_SIGNAL: J2.2, J3.2, Rf5.2
unnamed: CSn1.2, RSn2.1
unnamed: CSn2.2, RSn1.1
unnamed: Cf2.1, Rf2.2
unnamed: Cf4.1, Rf4.2
unnamed: Ci1.1, R1.2
unnamed: Ci2.1, R5.2
unnamed: Cin1.2, RB1.1, Rin1.2
unnamed: Cin2.2, RB2.1, Rin2.2
unnamed: D1.2 (A), R2.1
unnamed: D2.2 (A), R3.1
unnamed: J4.3, R4.1
unnamed: J11.3, R6.1
unnamed: Q1.1 (B), Rf5.1
unnamed: Q1.3 (C), Rf6.2
unnamed: Cf1.1, RB1.2, U2.8 (+)
unnamed: Cf2.2, R1.1, Rf1.2, U2.7 (-)
unnamed: Cf3.1, RB2.2, U2.13 (+)
unnamed: Cf4.2, R5.1, Rf3.2, U2.12 (-)
PGND: C1.2, C2.2, C3.1, C4.1, C5.2, C6.1, C7.2, C8.2, C9.2, CSn1.1, CSn2.1, D2.1 (K), J4.1, J5.1, J6.2, J8.1, J11.1, R2.2, R4.2, R6.2, U2.5 (GND), U2.10 (GND)
SIGGND: Ci1.2, J4.2
SIGGND2: Ci2.2, J11.2
VM: C3.2, C4.2, C6.2, D1.1 (K), J6.3, Q1.2 (E), U2.4 (V-)
VP: C1.1, C2.1, C5.1, C7.1, C8.1, C9.1, J6.1, R3.2, U2.2 (V+), U2.15 (V+)
